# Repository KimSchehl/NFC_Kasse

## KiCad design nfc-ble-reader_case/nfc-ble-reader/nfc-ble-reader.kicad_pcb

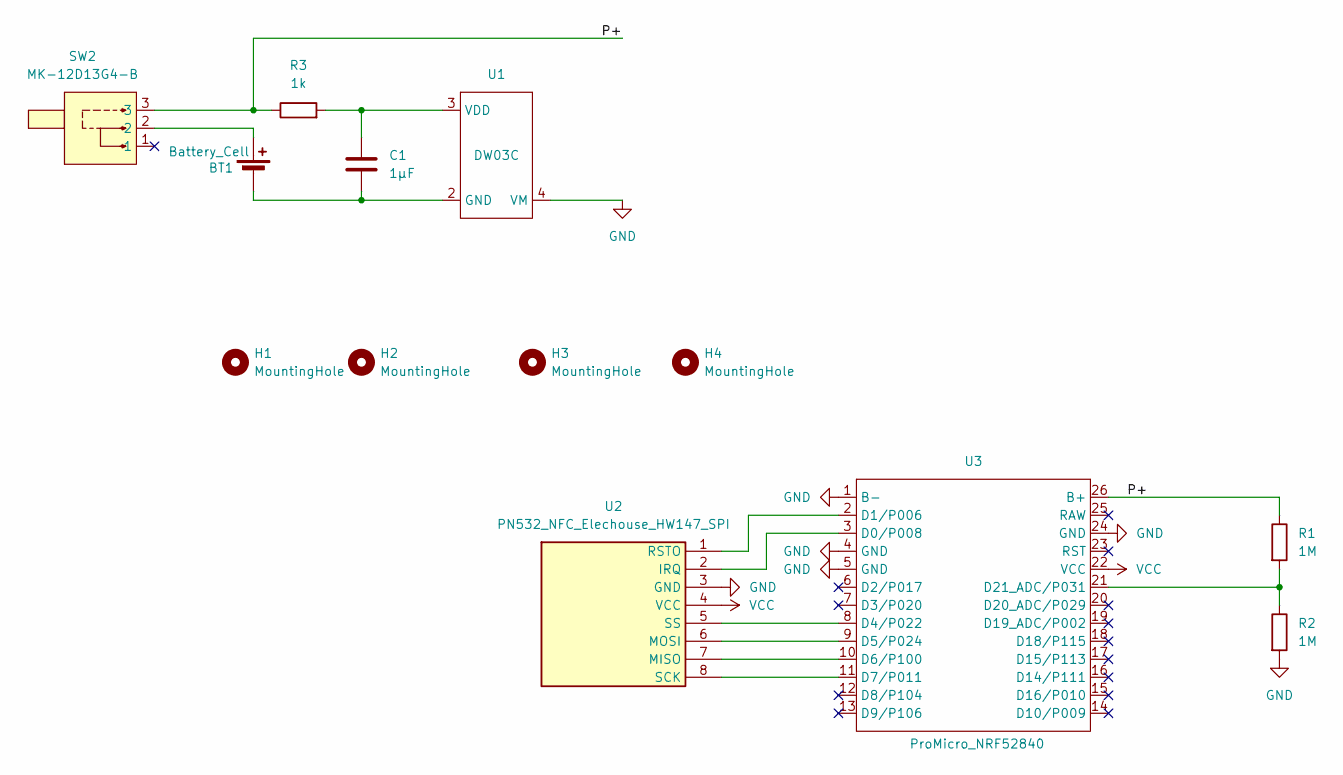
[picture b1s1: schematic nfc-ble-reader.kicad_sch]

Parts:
BT1: Battery_Cell; BATTERY-SMD_18650-1S-L77.1-W20.7-1; LCSC Part C2988620
C1: 1µF; C_0805_2012Metric_Pad1.18x1.45mm_HandSolder; LCSC Part C46653
H1, H2: MountingHole; MountingHole_3.2mm_M3
H3, H4: MountingHole; MountingHole_6.4mm_M6
R1, R2: 1M; R_0805_2012Metric_Pad1.20x1.40mm_HandSolder; LCSC Part C2907302
R3: 1k; R_0805_2012Metric_Pad1.20x1.40mm_HandSolder; LCSC Part C2907232
SW2: MK-12D13G4-B; SW-TH_MK-12D13G4-B; MPN MK-12D13G4-B; LCSC Part C20611678
U1: DW03C; SOT-23-5_HandSoldering; LCSC Part C42380663
U2: PN532_NFC_Elechouse_HW147_SPI; PinSocket_1x08_P2.54mm_Vertical
U3: ProMicro_NRF52840

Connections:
/P+: R1.1, R3.1, SW2.3, U3.26 (B+)
GND: R2.2, U1.4 (VM), U2.3 (GND), U3.1 (B-), U3.4 (GND), U3.5 (GND), U3.24 (GND)
unnamed: BT1.1 (+), SW2.2
unnamed: BT1.2 (-), C1.2, U1.2 (GND)
unnamed: C1.1, R3.2, U1.3 (VDD)
unnamed: U2.2 (IRQ), U3.3 (D0/P008)
unnamed: U2.7 (MISO), U3.10 (D6/P100)
unnamed: U2.6 (MOSI), U3.9 (D5/P024)
unnamed: U2.1 (RSTO), U3.2 (D1/P006)
unnamed: U2.8 (SCK), U3.11 (D7/P011)
unnamed: U2.5 (SS), U3.8 (D4/P022)
unnamed: R1.2, R2.1, U3.21 (D21_ADC/P031)
VCC: U2.4 (VCC), U3.22 (VCC)

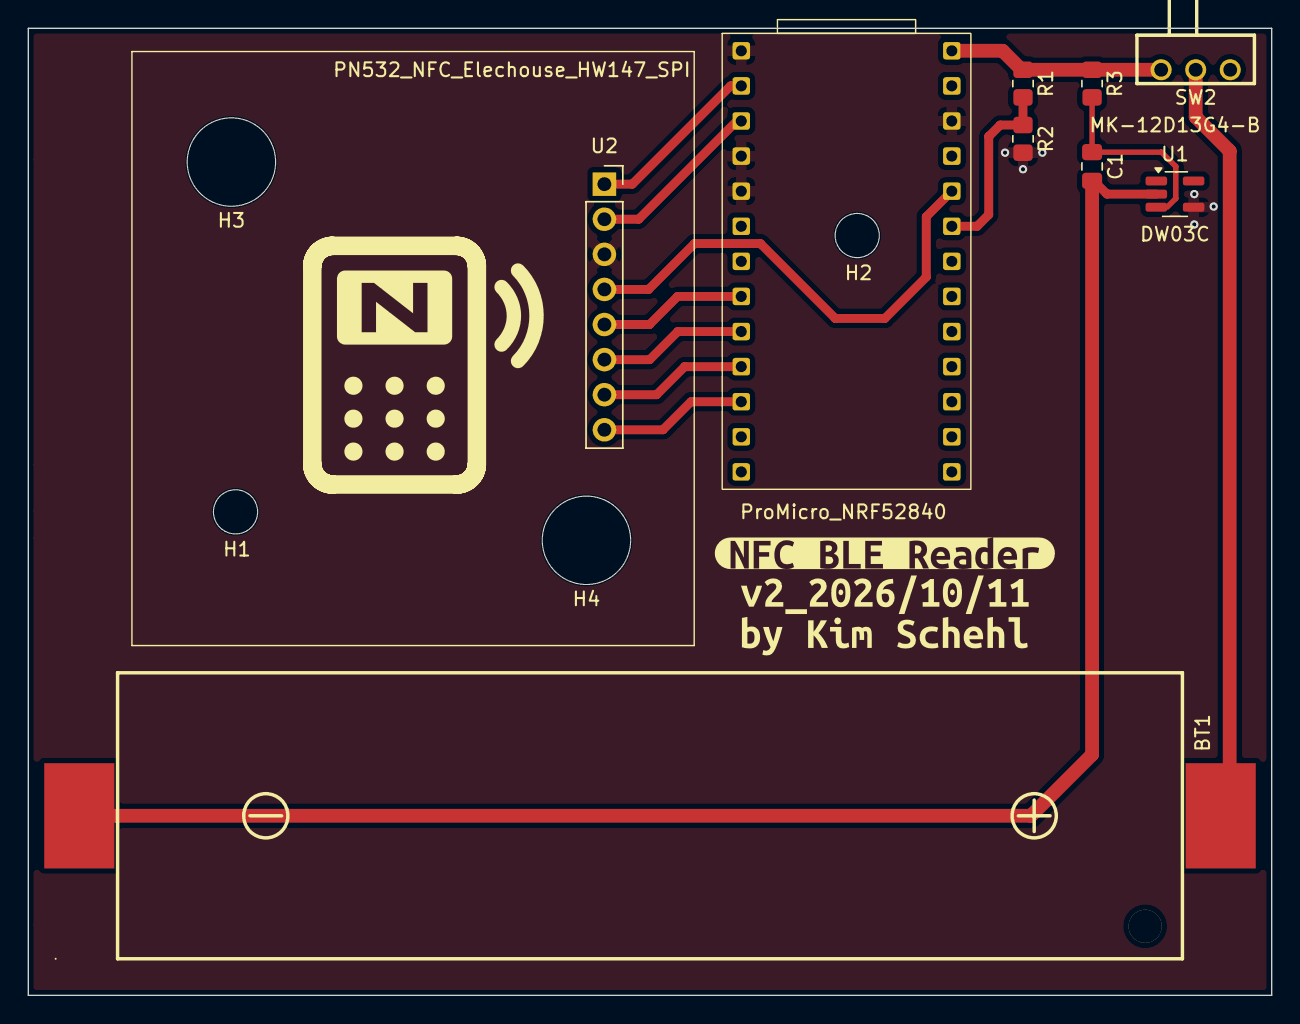
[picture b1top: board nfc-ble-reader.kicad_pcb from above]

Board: 2 copper layers, 90.0 x 70.0 mm, 16 parts (0 on the bottom side), 13 nets.

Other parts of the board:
kibuzzard-6A8E2BDD: G***; kibuzzard-6A8E2BDD
kibuzzard-6A8E2C5E: G***; kibuzzard-6A8E2C5E
kibuzzard-6ACBD38F: G***; kibuzzard-6ACBD38F

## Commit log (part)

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2026-05-13 Base Init.
2026-05-14 backend start with python install build and deploy with version numbers App icon
2026-05-15 Claude.md für Wissens Sync zwischen IDE's
2026-05-16 Tablet Appbar fix
2026-05-17 App Update fix
2026-05-17 NFC Tag Pfand Logic
2026-05-17 Final working fix for inApp update
2026-06-08 Booking Button in Save screen Reset credit display after booking
2026-06-08 added statistics revenue dynamic cart Dynamic Text size dynamic button columns Statistics ignore for cash inserts
2026-06-10 created Web app Reset event Button Better Topup Buttons QR code and download Page for APK
2026-06-10 feat: DB backup on startup, chip overview tab, connection indicator, improved error messages
    - Auto-backup kasse.db on every backend start (keeps last 5, stored in backups/)
    - New /api/customers endpoints: chip list + balance summary (active chips, total balance, pending deposit, topup/payout totals)
    - Statistics screen: third tab "Chips" with summary cards, searchable chip list, active/available status
    - AppBar connection indicator (WiFi icon) polling /health every 10 s; red on disconnect
    - formatApiError() converts raw DioExceptions to German user-friendly messages across login, users, and stats screens
2026-06-11 Log Files for backend
2026-06-12 added user defined colors added user defined article positions
